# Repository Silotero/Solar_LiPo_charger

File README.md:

# Solar_LiPo_charger
Solar panel battery charger

This is a battery charger that uses solar panels for the charging. It has a max charging input to the batteries of 4 A. It is also capable of outputing up to 15W of power at 5V 3A at its USB-C port. It also has a screw terminal with the same output capabilities.

The charging IC that takes care of taking the solar input (which must be 2 panels in series, the rest, up to 20 of such pairs, in parallel), making the constant-current/constant-voltage work is the CN3791. The IC responsible for making sure that the batteries don't get overcharged, overdischarged or shorted is the AP9101CK6. It also uses the PAM2423 boost converter to achieve the 5V output on the screw terminal as well as the USB-C port. The announcement of the USB-C capabilities is done via 10k ohm resistors pulled up to VCC on the CC pins.

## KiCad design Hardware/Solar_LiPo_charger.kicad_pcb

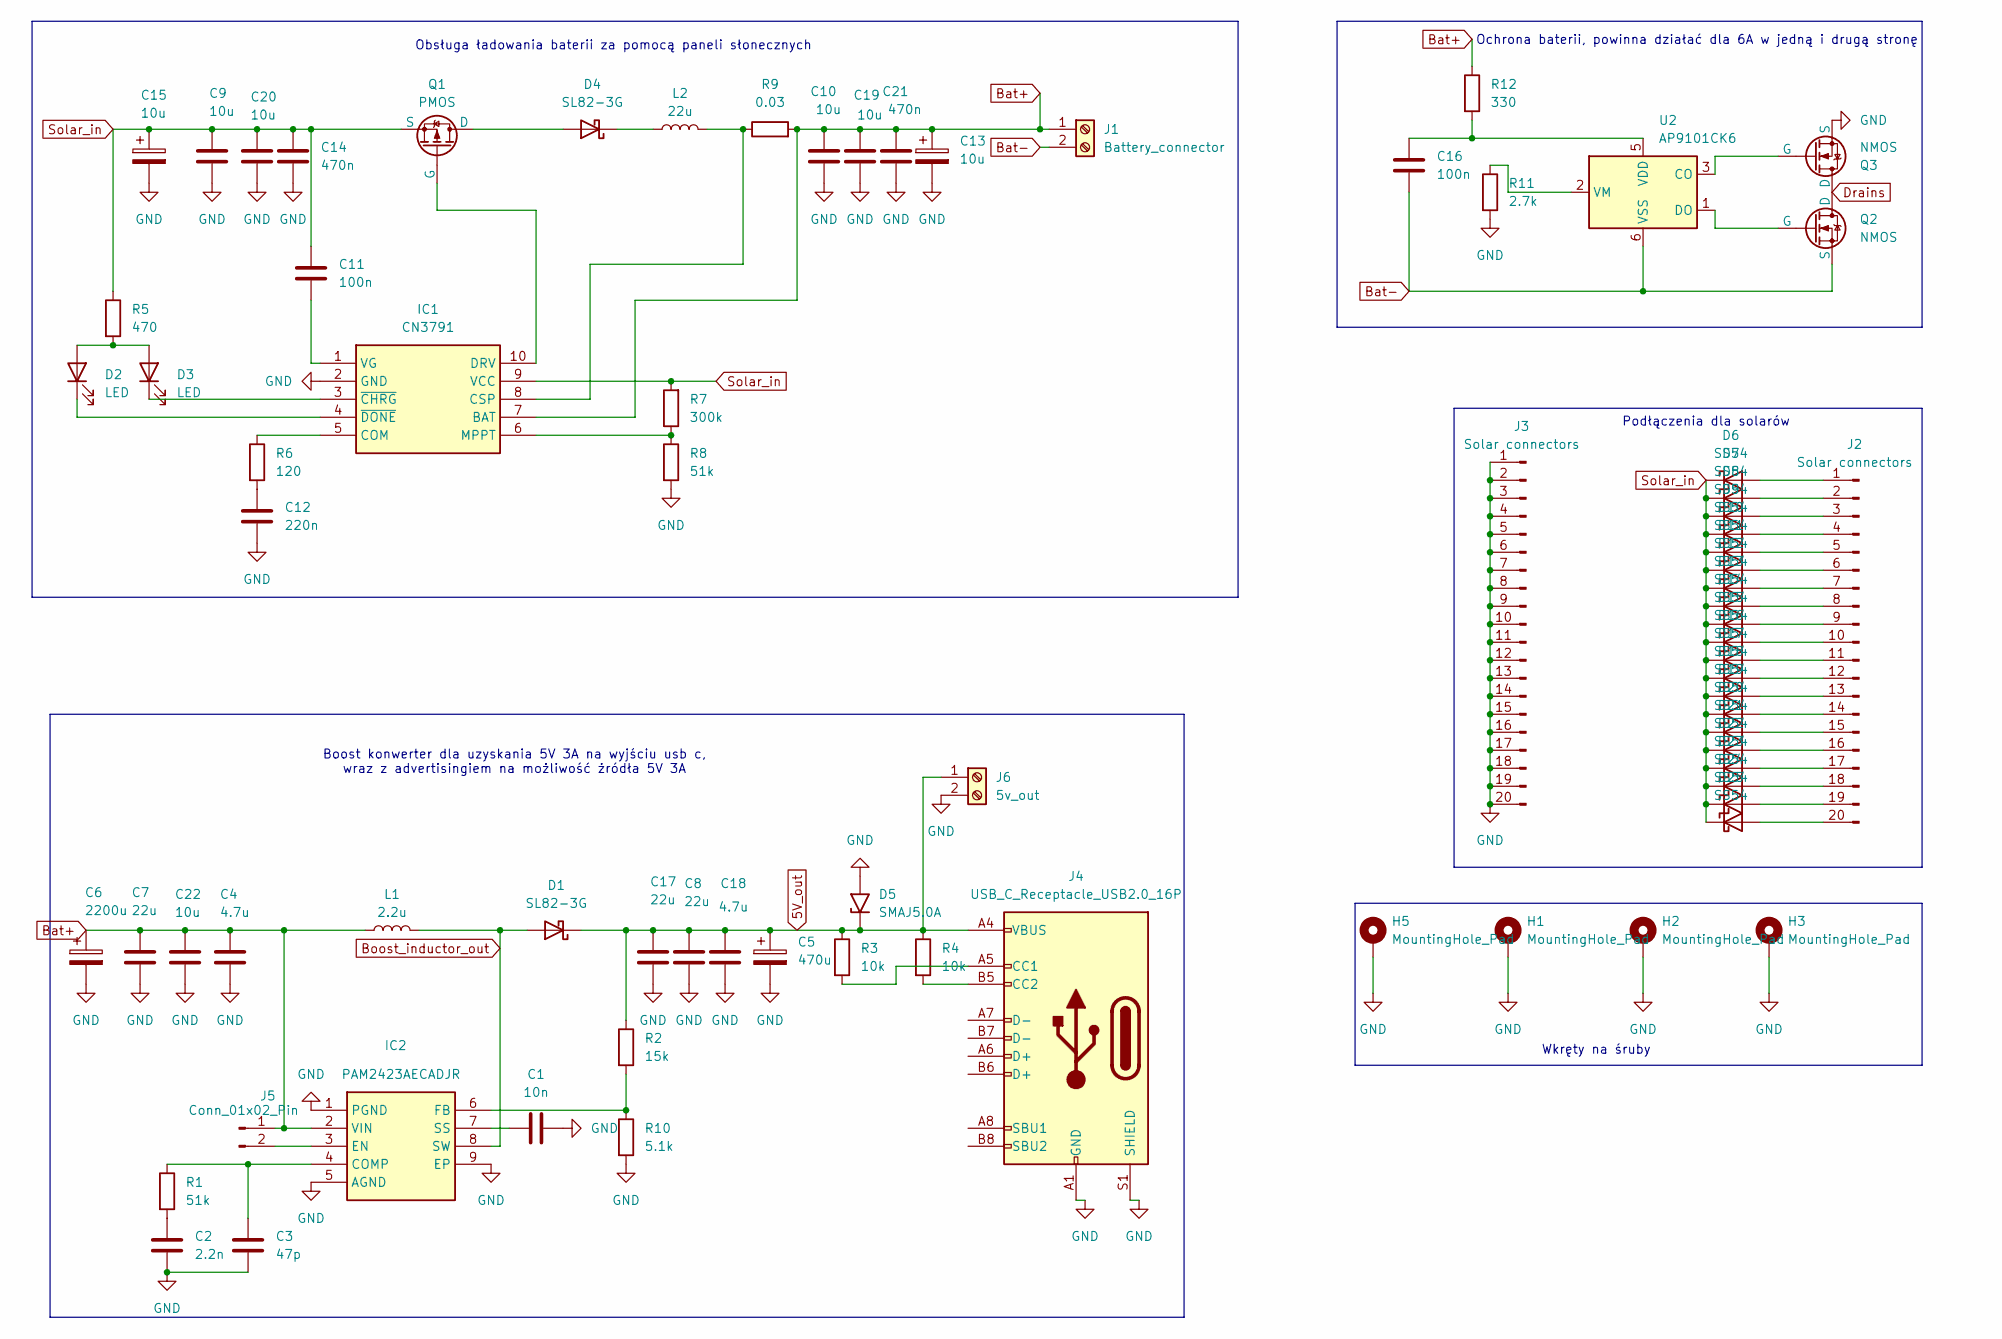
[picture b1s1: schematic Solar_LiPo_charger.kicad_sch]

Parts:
C1: 10n; C_0603_1608Metric
C2: 2.2n; C_0603_1608Metric
C3: 47p; C_0603_1608Metric
C4, C18: 4.7u; C_0603_1608Metric
C5: 470u; CP_Radial_D10.0mm_P5.00mm
C6: 2200u; CP_Radial_D10.0mm_P5.00mm
C7, C8, C17: 22u; C_0603_1608Metric
C9, C10, C19, C20, C22: 10u; C_0603_1608Metric
C11, C16: 100n; C_0603_1608Metric
C12: 220n; C_0603_1608Metric
C13, C15: 10u; CP_Radial_D4.0mm_P2.00mm
C14, C21: 470n; C_0603_1608Metric
D1, D4: SL82-3G; D_SMC
D2, D3: LED; D_0603_1608Metric
D5: SMAJ5.0A; D_SMA
D6, D7, D8, D9, D10, D11, D12, D13, D14, D15, D16, D17, D18, D19, D20, D21, D22, D23, D24, D25: SS54; D_SMA
H1, H2, H3, H5: MountingHole_Pad; MountingHole_2.2mm_M2_DIN965_Pad
IC1: CN3791; SOP100P600X175-10N; Manufacturer_Part_Number CN3791
IC2: PAM2423AECADJR; PAM2421AECADJR; Manufacturer_Part_Number PAM2421AECADJR; Mouser Part Number 621-PAM2421AECADJR
J1: Battery_connector; TerminalBlock_Phoenix_MKDS-1,5-2-5.08_1x02_P5.08mm_Horizont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
J2, J3: Solar connectors; PinHeader_1x20_P2.54mm_Vertical
J4: USB_C_Receptacle_USB2.0_16P; USB_C_Receptacle_GCT_USB4105-xx-A_16P_TopMnt_Horizontal
J5: Conn_01x02_Pin; PinHeader_1x02_P1.27mm_Vertical
J6: 5v_out; TerminalBlock_Phoenix_MKDS-1,5-2-5.08_1x02_P5.08mm_Horizont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
L1: 2.2u; DR127
L2: 22u; HCM1A1307V2-220-R
Q1: PMOS; SO-8_3.9x4.9mm_P1.27mm
Q2, Q3: NMOS; SOP-8_3.76x4.96mm_P1.27mm
R1, R8: 51k; R_0805_2012Metric
R2: 15k; R_0805_2012Metric
R3, R4: 10k; R_0805_2012Metric
R5: 470; R_0805_2012Metric
R6: 120; R_0805_2012Metric
R7: 300k; R_0805_2012Metric
R9: 0.03; R_1206_3216Metric
R10: 5.1k; R_0805_2012Metric
R11: 2.7k; R_0805_2012Metric
R12: 330; R_0805_2012Metric
U2: AP9101CK6; SOT-23-6

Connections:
5V_out: C5.1, C8.1, C17.1, C18.1, D1.1 (K), D5.1 (A1), J4.A4 (VBUS), J4.A9 (VBUS), J4.B4 (VBUS), J4.B9 (VBUS), J6.1, R2.1, R3.1, R4.1
Bat+: C4.1, C6.1, C7.1, C10.1, C13.1, C19.1, C21.1, C22.1, IC1.7 (BAT), IC2.2 (VIN), J1.1, J5.1, L1.1, R9.2, R12.1
Bat-: C16.2, J1.2, Q2.3 (S), U2.6 (VSS)
Boost_inductor_out: D1.2 (A), IC2.8 (SW), L1.2
Drains: Q2.1 (D), Q3.1 (D)
GND: C1.2, C2.2, C3.2, C4.2, C5.2, C6.2, C7.2, C8.2, C9.2, C10.2, C12.2, C13.2, C14.2, C15.2, C17.2, C18.2, C19.2, C20.2, C21.2, C22.2, D5.2 (A2), H1.1, H2.1, H3.1, H5.1, IC1.2 (GND), IC2.1 (PGND), IC2.5 (AGND), IC2.9 (EP), J3.1, J3.2, J3.3, J3.4, J3.5, J3.6, J3.7, J3.8, J3.9, J3.10, J3.11, J3.12, J3.13, J3.14, J3.15, J3.16, J3.17, J3.18, J3.19, J3.20, J4.A1 (GND), J4.A12 (GND), J4.B1 (GND), J4.B12 (GND), J4.S1 (SHIELD), J6.2, Q3.3 (S), R8.2, R10.2, R11.2
unnamed: C2.1, R1.2
unnamed: C12.1, R6.2
unnamed: D2.2 (A), D3.2 (A), R5.2
unnamed: D2.1 (K), IC1.4 (~DONE)
unnamed: D3.1 (K), IC1.3 (~CHRG)
unnamed: D4.2 (A), Q1.1 (D)
unnamed: D4.1 (K), L2.1
unnamed: D6.2 (A), J2.1
unnamed: D7.2 (A), J2.2
unnamed: D8.2 (A), J2.3
unnamed: D9.2 (A), J2.4
unnamed: D10.2 (A), J2.5
unnamed: D11.2 (A), J2.6
unnamed: D12.2 (A), J2.7
unnamed: D13.2 (A), J2.8
unnamed: D14.2 (A), J2.9
unnamed: D15.2 (A), J2.10
unnamed: D16.2 (A), J2.11
unnamed: D17.2 (A), J2.12
unnamed: D18.2 (A), J2.13
unnamed: D19.2 (A), J2.14
unnamed: D20.2 (A), J2.15
unnamed: D21.2 (A), J2.16
unnamed: D22.2 (A), J2.17
unnamed: D23.2 (A), J2.18
unnamed: D24.2 (A), J2.19
unnamed: D25.2 (A), J2.20
unnamed: IC1.5 (COM), R6.1
unnamed: IC1.8 (CSP), L2.2, R9.1
unnamed: IC1.10 (DRV), Q1.2 (G)
unnamed: IC1.6 (MPPT), R7.1, R8.1
unnamed: C11.2, IC1.1 (VG)
unnamed: C3.1, IC2.4 (COMP), R1.1
unnamed: IC2.3 (EN), J5.2
unnamed: IC2.6 (FB), R2.2, R10.1
unnamed: C1.1, IC2.7 (SS)
unnamed: J4.A5 (CC1), R3.2
unnamed: J4.B5 (CC2), R4.2
unnamed: Q2.2 (G), U2.1 (DO)
unnamed: Q3.2 (G), U2.3 (CO)
unnamed: C16.1, R12.2, U2.5 (VDD)
unnamed: R11.1, U2.2 (VM)
Solar_in: C9.1, C11.1, C14.1, C15.1, C20.1, D6.1 (K), D7.1 (K), D8.1 (K), D9.1 (K), D10.1 (K), D11.1 (K), D12.1 (K), D13.1 (K), D14.1 (K), D15.1 (K), D16.1 (K), D17.1 (K), D18.1 (K), D19.1 (K), D20.1 (K), D21.1 (K), D22.1 (K), D23.1 (K), D24.1 (K), D25.1 (K), IC1.9 (VCC), Q1.3 (S), R5.1, R7.2

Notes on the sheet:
Ochrona baterii, powinna działać dla 6A w jedną i drugą stronę
Podłączenia dla solarów
Boost konwerter dla uzyskania 5V 3A na wyjściu usb c, wraz z advertisingiem na możliwość żródła 5V 3A
Obsługa ładowania baterii za pomocą paneli słonecznych
Wkręty na śruby

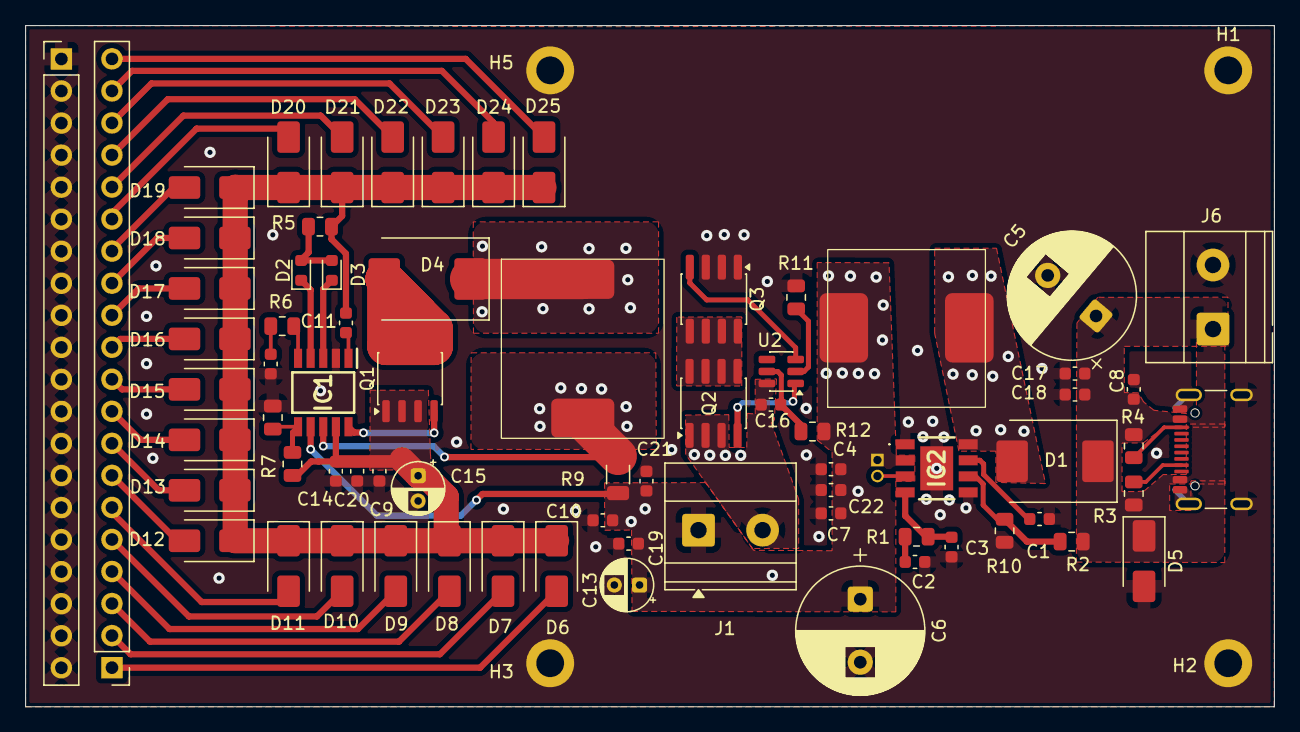
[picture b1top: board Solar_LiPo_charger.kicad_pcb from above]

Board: 2 copper layers, 99.0 x 54.0 mm, 77 parts (0 on the bottom side), 49 nets.

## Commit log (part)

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2026-04-07 Added finished kicad project files
